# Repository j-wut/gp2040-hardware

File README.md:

# Open Stick Community hardware repo

This repository is a collection of open-source hardware designs which have been submitted to the project.

# Designs

3D Prints

- [3D Printable Stand - Small](/3D%20Prints/3D%20Printable%20Stand/README.md) - Designed by TheTrain
- [3D Printable Stand - Large](/3D%20Prints/3D%20Printable%20Stand/README.md) - Designed by TheTrain
- [3D Printable Fightstick Case](/3D%20Prints/Fightstick%20Case/README.md) - Designed by TheTrain
- [3D Printable Open Stick Mini](/3D%20Prints/Open%20Stick%20Mini/README.md) - Designed by TheTrain
- [3D Printable Fightstick Case XL](/3D%20Prints/Fightstick%20Case/Community%20submissions/3D%20print%20files/Fightstick%20XL/Open%20Stick%20XL%20-%20Main%20Frame%20(x4%20Buttons).stl) - Designed by Lucipher
- [3D Printable Open Stick Modular](/3D%20Prints/Open%20Stick%20Modular%20(OSM)/README.md) - Designed by TheTrain
- [3D Printable Open Stick Modular - Mini](/3D%20Prints/Open%20Stick%20Modular%20-%20Mini%20(OSM-Mini)/README.md) - Designed by TheTrain
- [3D Printable Open Stick Modular - Slim](/3D%20Prints/Open%20Stick%20Modular%20-%20Slim%20(OSM-Slim)/README.md) - Designed by TheTrain
- [3D Printable Open Stick Astro](/3D%20Prints/Open%20Stick%20Astro%20(OSASTRO)/README.md) - Designed by TheTrain
- [3D Printable OSBMX v2 Buttons](/3D%20Prints/OSBMX%20v2/README.md) - Designed by TheTrain
- [3D Printable OSBLP v2 Buttons](/3D%20Prints/OSBLP%20v2/README.md) - Designed by TheTrain
- [3D Printable OSBMX v2 SiTong Edition Buttons](/3D%20Prints/OSBMX%20v2/Community%20submissions/OSBMX%20v2%20-%20SiTong%20Edition/README.md) - Designed by TheTrain (remixed from the OSBLP v2 by TheTrain)
- [3D Printable OSBLP v2 SiTong Edition Buttons](/3D%20Prints/OSBLP%20v2/Community%20submissions/OSBLP%20v2%20-%20SiTong%20Edition/README.md) - Designed by TheTrain (remixed from the OSBLP v2 by TheTrain)
- [3D Printable OSBHE v2 Buttons](/3D%20Prints/OSBHE%20v2/README.md) - Designed by TheTrain
- [3D Printable OSB Plug](/3D%20Prints/OSB%20Plug/README.md) - Designed by TheTrain
- [3D Printable OSB Analog Stick](/3D%20Prints/OSB%20Analog%20Stick/README.md) - Designed by TheTrain
- [Open Source Arcade Stand - OSAS](/3D%20Prints/Open%20Source%20Arcade%20Stand%20(OSAS)/README.md) - Designed by TheTrain

GP2040-CE Official Boards

- [RP2040 Advanced Breakout Board v5.6E with USB Passthrough](/Boards/GP2040-CE%20Official%20Boards/RP2040%20Advanced%20Breakout%20Board/RP2040%20Advanced%20Breakout%20Board%20-%20Passthrough/README.md) - Designed by TheTrain
- [RP2040 Advanced Breakout Board v5.2E (no USB Passthrough)](/Boards/GP2040-CE%20Official%20Boards/RP2040%20Advanced%20Breakout%20Board/RP2040%20Advanced%20Breakout%20Board/README.md) - Designed by TheTrain
- [RP2040 Basic Breakout Board v5.4E with USB Passthrough](/Boards/GP2040-CE%20Official%20Boards/RP2040%20Basic%20Breakout%20Board/RP2040%20Basic%20Breakout%20Board%20-%20Passthrough/README.md) - Designed by TheTrain
- [RP2040 Basic Breakout Board v5.4E (no USB Passthrough)](/Boards/GP2040-CE%20Official%20Boards/RP2040%20Basic%20Breakout%20Board/RP2040%20Basic%20Breakout%20Board/README.md) - Designed by TheTrain
- [RP2040 Mini Breakout Board v7.5E with USB Passthrough](/Boards/GP2040-CE%20Official%20Boards/RP2040%20Mini%20Breakout%20Board/RP2040%20Mini%20Breakout%20Board%20-%20Passthrough/README.md) - Designed by TheTrain
- [RP2040 Mini Breakout Board v7.3E (no USB Passthrough)](/Boards/GP2040-CE%20Official%20Boards/RP2040%20Mini%20Breakout%20Board/RP2040%20Mini%20Breakout%20Board/README.md) - Designed by TheTrain
- [RP2040 Quick Solder Breakout Board v1.0 (no USB Passthrough)](/Boards/GP2040-CE%20Official%20Boards/RP2040%20Quick%20Solder%20Breakout%20Board/README.md) - Designed by TheTrain

GP2040-CE Official Controllers

- [ARC Accessibility Controller](/Boards/GP2040-CE%20Official%20Controllers/ARC%20Accessibility%20Controller/README.md) - Designed by TheTrain
- [Flatbox Rev 5 RGB](/Boards/GP2040-CE%20Official%20Controllers/Flatbox%20Rev%205%20RGB/README.md) - Remixed by TheTrain from the Flatbox Rev 5 by Jfedor
- [Flatbox Rev 5 Passthrough](/Boards/GP2040-CE%20Official%20Controllers/Flatbox%20Rev%205%20Passthrough/README.md) - Remixed by TheTrain from the Flatbox Rev 5 by Jfedor
- [Open_Core0 v2.0](/Boards/GP2040-CE%20Official%20Controllers/Open_Core0/README.md) - Designed by TheTrain
- [Open_Core0 WASD v2.0](/Boards/GP2040-CE%20Official%20Controllers/Open_Core0%20WASD/README.md) - Designed by TheTrain
- [Open_Core0 MIXUP](/Boards/GP2040-CE%20Official%20Controllers/Open_Core0%20MIXUP/README.md) - Designed by TheTrain
- [Zero_Rhythm v1.0](/Boards/GP2040-CE%20Official%20Controllers/Zero%20Rhythm/README.md) - Designed by TheTrain
- [Pocket Pad](/Boards/GP2040-CE%20Official%20Controllers/Pocket%20Pad/README.md) - Designed by TheTrain
- [Pocket Pad WASD](/Boards/GP2040-CE%20Official%20Controllers/Pocket%20Pad%20WASD/README.md) - Designed by TheTrain
- [Mini Pad](/Boards/GP2040-CE%20Official%20Controllers/Mini%20Pad/README.md) - Designed by TheTrain

Retail Stick Replacement Boards

- [Hori Fighting Edge PS3 (FE PS3)](/Boards/Retail%20Stick%20Replacement%20Boards/Hori%20Fighting%20Edge%20PS3%20(FE%20PS3)/README.md) - Designed by TheTrain
- [Hori Fighting Edge PS4 (FE PS4)](/Boards/Retail%20Stick%20Replacement%20Boards/Hori%20Fighting%20Edge%20PS4%20(FE%20PS4)/README.md) - Designed by TheTrain
- [Hori Real Arcade Pro N PS4 (RAP N PS4)](/Boards/Retail%20Stick%20Replacement%20Boards/Hori%20Real%20Arcade%20Pro%20N%20PS4%20(RAP%20N%20PS4)/README.md) - Designed by TheTrain
- [Hori Real Arcade Pro VLX PS3 (RAP VLX PS3)](/Boards/Retail%20Stick%20Replacement%20Boards/Hori%20Real%20Arcade%20Pro%20VLX%20PS3%20(RAP%20VLX%20PS3)/README.md) - Designed by TheTrain
- [SEGA Dreamcast Twin Stick (with USB Passthrough)](/Boards/Retail%20Stick%20Replacement%20Boards/SEGA%20Dreamcast%20Twin%20Stick%20(with%20USB%20Passthrough)/README.md) - Designed by indigotrance

Supported Boards

- [Ghost Auth v2.0](/Boards/Supported%20Boards/Ghost%20Auth/README.md) - Designed by TheTrain
- [GP2040 Keyboard converter](/Boards/Supported%20Boards/GP2040%20Keyboard%20Converter/Waveshare%20Zero-PCB/README.md) - Designed by Infraredaces
- [USB Pasthrough Add-on Board](/Boards/Supported%20Boards/USB%20Passthrough%20Board/README.md) - Designed by TheTrain
- [Tiny USB Hub v1.2 - 2x USB with USB C](/Boards/Supported%20Boards/USB%20Hubs/Tiny%20USB%20Hub%20v1.2e/README.md) - Designed by TheTrain
- [Tiny USB Hub v1.3 - 2x USB Direct Connect](/Boards/Supported%20Boards/USB%20Hubs/Tiny%20USB%20Hub%20v1.3e/README.md) - Designed by TheTrain
- [Tiny USB Hub v1.3 v2 - 2x USB Direct Connect](/Boards/Supported%20Boards/USB%20Hubs/Tiny%20USB%20Hub%20v1.3e%20v2/README.md) - Designed by TheTrain
- [Tiny USB Hub v1.4 - 4x USB Direct Connect](/Boards/Supported%20Boards/USB%20Hubs/Tiny%20USB%20Hub%20v1.4e/README.md) - Designed by TheTrain
- [HE Breakout Board v1.1](/Boards/Supported%20Boards/HE%20Breakout%20Board/README.md) - Designed by TheTrain
- [RPBoy v1.0](/Boards/Supported%20Boards/RPBoy/README.md) - Designed by TheTrain
- [RPBoy Mini v2.0](/Boards/Supported%20Boards/RPBoy%20Mini/README.md) - Designed by TheTrain
- [Key Matrix Diode Adapter](/Boards/Supported%20Boards/Key%20Matrix%20Diode%20Adapter/README.md) - 44-switch keyboard-style matrix with N-key rollover for the RP2040 Advanced Breakout Board (USB Passthrough)

Miscellaneous

- [Haute42/COSMOX Bottom Foam](/Miscellaneous/Haute42%20COSMOX%20Bottom%20Foam/README.md) - Designed by TheTrain
- [Sanjuks V3 AM5 Adapter Plate](/Miscellaneous/Sanjuks%20V3%20AM5%20Adapter%20Plate/README.md) - Designed by TheTrain
- [Sanjuks Style Nobi Topper](/Miscellaneous/Sanjuks%20Style%20Nobi%20Topper/README.md) - Designed by TheTrain
- [Open LED Project - Sanwa 30mm RGB LEDs](/Miscellaneous/Open%20LED%20Project%20-%20Sanwa%2030mm%20RGB%20LED/README.md) - Designed by TheTrain
- [Open LED Project - Addressable RGB LED Light Bar](/Miscellaneous/Open%20LED%20Project%20-%20Addressable%20RGB%20LED%20Light%20Bar/README.md) - Designed by TheTrain
- [Nintendo Switch Art Cart](/Miscellaneous/Nintendo%20Switch%20Art%20Carts/README.md) - Designed by TheTrain, art template by TheTrain
- [Sanwa JLF Plate Cover](/Miscellaneous/Sanwa%20JLF%20Plate%20Cover/README.md) - Designed by TheTrain

Trains Vewlix Stuff

- [Vewlix Coin Return Adapter](/Trains%20Vewlix%20Stuff/Vewlix%20Coin%20Return%20Adapter/README.md) - Designed by TheTrain
- [Vewlix Coin Return Slot](/Trains%20Vewlix%20Stuff/Vewlix%20Coin%20Return%20Slot/README.md) - Designed by TheTrain
- [Vewlix Coin Mech](/Trains%20Vewlix%20Stuff/Vewlix%20Coin%20Mech/README.md) - Designed by TheTrain
- [Vewlix Stickers](/Trains%20Vewlix%20Stuff/Vewlix%20Stickers/README.md) - Remixes and customs by TheTrain
- [Vewlix Control Panel SiTong Adapter Rings](/Trains%20Vewlix%20Stuff/Vewlix%20Control%20Panel%20SiTong%20Adapter%20Rings/README.md) - Designed by TheTrain
- [Vewlix NESiCA NFC Reader](/Trains%20Vewlix%20Stuff/Vewlix%20NESiCA%20NFC%20Reader/README.md) - Designed by TheTrain
- [Vewlix Sub-Panel Art and Cut Files](/Trains%20Vewlix%20Stuff/Vewlix%20Sub-Panel%20Art%20and%20Cut%20Files/README.md) - Designed by Jermaine Davis

Trains Sim Racing Stuff

- [Logitech G PRO RS Wheel Hub wall mount](/Trains%20Sim%20Racing%20Stuff/Logitech%20G%20PRO%20RS%20Wheel%20Hub%20wall%20mount/README.md) - Designed by TheTrain
- [Logitech G PRO RS Wheel Hub 4040 mount](/Trains%20Sim%20Racing%20Stuff/Logitech%20G%20PRO%20RS%20Wheel%20Hub%204040%20mount/README.md) - Designed by TheTrain
- [Logitech G PRO RS Wheel Hub Shifter Pad Mod](/Trains%20Sim%20Racing%20Stuff/Logitech%20RS%20Wheel%20Hub%20Shifter%20Pad%20Mod/README.md) - Designed by TheTrain
- [Logitech G PRO RS Wheel Rim template](/Trains%20Sim%20Racing%20Stuff/Logitech%20G%20PRO%20RS%20Wheel%20Rim%20template/README.md) - Designed by TheTrain
- [Wind Sim](/Trains%20Sim%20Racing%20Stuff/Wind%20Sim/README.md) - Designed by TheTrain
- [LapTimer](/Trains%20Sim%20Racing%20Stuff/Laptimer/README.md) - Designed by TheTrain
- [Porsche GT3 R Plate](/Trains%20Sim%20Racing%20Stuff/Porsche%20911%20GT3%20R%20plate/README.md) - Designed by TheTrain

Trains Theatrhythm Stuff
- [Theatrhythm - All-Star Carnival Manual](/Trains%20Theatrhythm%20Stuff/Theatrhythm%20Manual/Theatrhythm%20-%20All-Star%20Carnival%20-%20Manual.pdf)
- [Theatrhythm - All-Star Carnival JLF Shaft](/Trains%20Theatrhythm%20Stuff/Theatrhythm%20JLF%20shaft/README.md) - Designed by LayerShift
- [Theatrhythm - All-Star Carnival Side Plexi Art](/Trains%20Theatrhythm%20Stuff/Theatrhythm%20ASC%20Arcade%20Cabinet%20Art/Theatrhythm%20ASC%20Side%20Plexi%20Art/README.md) - Designed by TheTrain
- [Theatrhythm - All-Star Carnival Front Control Panel Art](/Trains%20Theatrhythm%20Stuff/Theatrhythm%20ASC%20Arcade%20Cabinet%20Art/Theatrhythm%20ASC%20Front%20Control%20Panel%20Art/README.md) - Designed by TheTrain
- [Theatrhythm - All-Star Carnival NESiCA Reader Art](/Trains%20Theatrhythm%20Stuff/Theatrhythm%20ASC%20Arcade%20Cabinet%20Art/Theatrhythm%20ASC%20NESiCA%20Reader%20Art/README.md) - Designed by TheTrain
- [Theatrhythm - All-Star Carnival Coin Sticker Art](/Trains%20Theatrhythm%20Stuff/Theatrhythm%20ASC%20Arcade%20Cabinet%20Art/Theatrhythm%20ASC%20Coin%20Sticker%20Art/README.md) - Designed by TheTrain

Trains Arcade Machine Manual Stuff

- [Taito Vewlix L - Manual - Part 1](/Trains%20Vewlix%20Stuff/Vewlix%20Manual/Taito%20Vewlix%20L%20-%20Manual%20-%20Part%201.pdf)
- [Taito Vewlix L - Manual - Part 2](/Trains%20Vewlix%20Stuff/Vewlix%20Manual/Taito%20Vewlix%20L%20-%20Manual%20-%20Part%202.pdf)
- [Taito Vewlix L - Manual - Part 3](/Trains%20Vewlix%20Stuff/Vewlix%20Manual/Taito%20Vewlix%20L%20-%20Manual%20-%20Part%203.pdf)
- [Theatrhythm - All-Star Carnival](/Trains%20Theatrhythm%20Stuff/Theatrhythm%20Manual/Theatrhythm%20-%20All-Star%20Carnival%20-%20Manual.pdf)

Tutorials

- [Focus Attack RGB LED Board Configuration](/Tutorials/Focus%20Attack%20LED%20Board%20Configuration/README.md) for the [RP2040 Advanced Breakout Board v5.6](/Boards/GP2040-CE%20Official%20Boards/RP2040%20Advanced%20Breakout%20Board/RP2040%20Advanced%20Breakout%20Board%20-%20Passthrough/README.md) - Written by TheTrain
- [USB Passthrough Add-on Board Installation](/Tutorials/USB%20Passthrough%20Board%20Installation/README.md) - Written by TheTrain
- [Logitech RS Wheel Hub Shifter Pad Mod](/Tutorials/Logitech%20RS%20Wheel%20Hub%20Shifter%20Pad%20Mod/README.md) - Written by TheTrain

Vendor Resources

- [GP2040-CE Logo Files](/Vendor%20Resources/GP2040-CE%20Logo%20files/README.md)

# Contributing

Any design submitted to this repository must be submitted by the original copyright holder and include a [license](#licensing). If your license requires attribution, you must provide details on how to appropriately attribute the design.

# Copyright

All copyrights are retained by the original author(s) unless the copyright is explicitly transferred to the Open Stick Community.

# Licensing

Check the LICENSE of each design for details on how the design can be used.

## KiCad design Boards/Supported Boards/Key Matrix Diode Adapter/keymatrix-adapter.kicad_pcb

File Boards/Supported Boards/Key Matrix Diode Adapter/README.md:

# Key matrix diode adapter

A board that turns the 20-pin header of the **RP2040 Advanced Breakout Board (USB Passthrough edition)** into 44
matrix switch inputs with full N-key rollover: all 15 button pins as 4 rows x 11 columns. It goes with the
`RP2040AdvancedBreakoutBoardUSBPassthroughMatrix` firmware config in
[j-wut/GP2040-CE](https://github.com/j-wut/GP2040-CE) (keyboard matrix support).

- 91 x 93.4 mm, 2 layers, 0.2 mm tracks, all through-hole connectors plus 44 SOD-123 diodes.
- **J1** connects to the breakout board's 20-pin header with a straight 20-pin IDC ribbon cable (pin 1 to pin 1).
- **J2-J5** are two pairs of 20-pin switch connectors (A and B).
- **J6-J13** are screw terminals in four rows, two behind each other on each side of the headers: two per switch, in the same order as the connector pins. The
  last 4 switches are on screw terminals only.
- One 1N4148W diode per switch, already on the board. No diodes are needed in the wiring.

## How a switch is wired

Every switch has a **slot** with two contacts, A and B. Wire the switch between them, either on the connector pair
(pin N on A and pin N on B) or on its two neighbouring screw terminals. Both reach the same switch. A switch has no
polarity, so either wire can go to A.

- **A** goes through the switch's diode to its row.
- **B** is its column. All the B contacts of one column are connected on the board, so a harness can share them.
  A contacts must never be shared.

Do not plug a normal 20-pin button harness (buttons wired to ground) into the switch connectors.

## Slot order

Both pairs have the same order. **Pair 1 follows the breakout's 20-pin header.** Each of its 15 button pins
carries the switch that defaults to that pin's button, so a harness made for the breakout's pinout lines up:

- Pin 5 is K4 (L2), pin 13 is P1 (B3), pin 20 is U (Up), and so on.

The breakout's 5 power and ground positions (pins 1-4 and 9) carry five more switches. Pair 2 carries the next
20 in row order, and the last 4 are on screw terminals only. R*n*C*m* is the switch in row *n*, column *m*, as listed in the web config (Add-ons > Keyboard
Matrix).

| Pin | Pair 1 (J2 A / J3 B) | Pair 2 (J4 A / J5 B) |
|-----|-----|-----|
| 1 | R2C5 | R2C10 |
| 2 | R2C6 | R2C11 |
| 3 | R2C7 | R3C1 |
| 4 | R2C8 | R3C2 |
| 5 | K4 (R1C1) | R3C3 |
| 6 | K3 (R1C2) | R3C4 |
| 7 | K2 (R1C3) | R3C5 |
| 8 | K1 (R1C4) | R3C6 |
| 9 | R2C9 | R3C7 |
| 10 | P4 (R1C5) | R3C8 |
| 11 | P3 (R1C6) | R3C9 |
| 12 | P2 (R1C7) | R3C10 |
| 13 | P1 (R1C8) | R3C11 |
| 14 | S2 (R1C9) | R4C1 |
| 15 | A1 (R1C10) | R4C2 |
| 16 | S1 (R1C11) | R4C3 |
| 17 | L (R2C1) | R4C4 |
| 18 | R (R2C2) | R4C5 |
| 19 | D (R2C3) | R4C6 |
| 20 | U (R2C4) | R4C7 |

Screw terminals only: R4C8, R4C9, R4C10, R4C11.

The screw terminals hold the same slots in the same order, A then B:

- above the headers, wire entry toward the top edge: the front row (at the edge) has pair 1 pins 1-11, the row
  behind it has pair 1 pins 12-20, then R4C8 and R4C9
- below the headers, wire entry toward the bottom edge: the front row (at the edge) has pair 2 pins 1-11, the row
  behind it has pair 2 pins 12-20, then R4C10 and R4C11
- every row reads left to right

Each slot's label is printed just behind its two screws. The rows are 6 mm apart, so the wires for a back row
go in over the diodes of the row in front.

GPIO 20-22 (A2, L3, R3 on the breakout's 4-pin harness) are not on the 20-pin header and stay ordinary buttons on
the breakout board. Don't wire anything else to the breakout's own K1-K4, P1-P4, S1, S2, A1, L, R, D, U terminals
while the adapter is connected: those GPIOs are matrix lines now.

## Signals

| J1 pin | Signal | Breakout label | | J1 pin | Signal | Breakout label |
|-----|--------|----|-|-----|--------|----|
| 1 | +5V | VCC | | 2 | +5V | VCC |
| 3 | GND | G | | 4 | GND | G |
| 5 | COL1 (GP5) | K4 | | 6 | COL2 (GP6) | K3 |
| 7 | COL3 (GP7) | K2 | | 8 | COL4 (GP8) | K1 |
| 9 | GND | G | | 10 | COL5 (GP9) | P4 |
| 11 | COL6 (GP10) | P3 | | 12 | COL7 (GP11) | P2 |
| 13 | COL8 (GP12) | P1 | | 14 | COL9 (GP13) | S2 |
| 15 | COL10 (GP14) | A1 | | 16 | COL11 (GP15) | S1 |
| 17 | ROW1 (GP16) | L | | 18 | ROW2 (GP17) | R |
| 19 | ROW3 (GP18) | D | | 20 | ROW4 (GP19) | U |

The pin numbers are the pad numbers of the 20-pin header on the breakout board's own design file (v5.6, in this
repository): pins 1 and 2 are +5 V, pin 20 is UP. `check.py` reads that file and checks J1 against it. Check pin 1
on your board before the first power-up anyway.

## Files

| File | What it is |
|------|------------|
| `keymatrix-adapter.kicad_sch`, `.kicad_pcb`, `.kicad_pro` | KiCad 7 project |
| `fab/gerbers/` | Gerbers and drill file for ordering the PCB |
| `fab/keymatrix-adapter-bom.csv` | Bill of materials |
| `fab/keymatrix-adapter-pos.csv` | Pick-and-place positions for the diodes |
| `fab/keymatrix-adapter-schematic.pdf` | Schematic |
| `generate.py`, `autoroute.py` | Build the schematic and the routed PCB from one parts and nets table |
| `check.py` | Runs the checks below and writes `fab/` |
| `simulate.py`, `sim-results.txt` | ngspice simulation of the full matrix through this board, and its results |

## Checks

`python3 generate.py && python3 check.py [path/to/GP2040-CE]` (needs KiCad 7 with its Python module) regenerates the
design and checks:

- J1's pin numbers match the 20-pin header on the breakout board's design file in this repository.
- KiCad DRC: no clearance or other violations, no unconnected pads.
- The schematic netlist (from `kicad-cli`) connects exactly the same pads as the PCB.
- Every one of the 44 switches has its own diode, cathode on the right row. Given a GP2040-CE checkout, the rows and
  columns must also match `KEY_MATRIX_ROW_PINS` / `KEY_MATRIX_COL_PINS` in the firmware board config.
- Every switch is on exactly one connector slot. Pair 1 is in breakout pin order. The screw terminals, read around
  the board, are in the same slot order as the connectors, with the terminal-only switches in order between them.

## Simulation

`python3 simulate.py` runs ngspice on the whole 4 x 11 matrix through this board: RP2040 pull-ups and pins, the ribbon
cable, the copper of every net on this PCB (measured from the board file), the 44 diodes, and the harness wiring
(each switch's own wire plus the column's B wire daisy-chained through its four switches). It scans the way the firmware
does and checks every read for several held-switch patterns, including all 44 held. Results:
[sim-results.txt](sim-results.txt).

| Wiring (ribbon / switch wire / column chain) | Press seen at the pin | Column recovery | Result with defaults |
|-----|-----|-----|-----|
| short: 0.15 m / 0.2 m / 1 m | 0.2 us | up to 10 us | pass |
| typical arcade stick: 0.3 m / 0.5 m / 3 m | 0.3 us | up to 19 us | pass |
| long cabinet: 1 m / 1 m / 6 m | 0.6 us | up to 34 us | pass |

`python3 simulate.py --trace trace.json` replays a GPIO timeline recorded from the firmware's own scan loop
instead of the fixed schedule: row drive and release events plus read times in, the voltage and logic level of
every column at each read out. The input format is in `run_trace()`.

Wire length adds no meaningful latency: a press shows up at the pin in under 0.6 us even with cabinet
wiring. What wiring does set is how long a released row's columns take to climb back through the RP2040's weak
pull-ups. The firmware waits a fixed **row delay** after each row for that (default 50 us, set in the web config
next to the settle time). With the defaults a full scan of all four rows takes about 224 us, well inside the 1 ms
between USB reports. Shorter wiring can use a smaller row delay; see `docs/keymatrix-sim/results.txt` in the firmware repository.

Not built or tested on hardware yet.

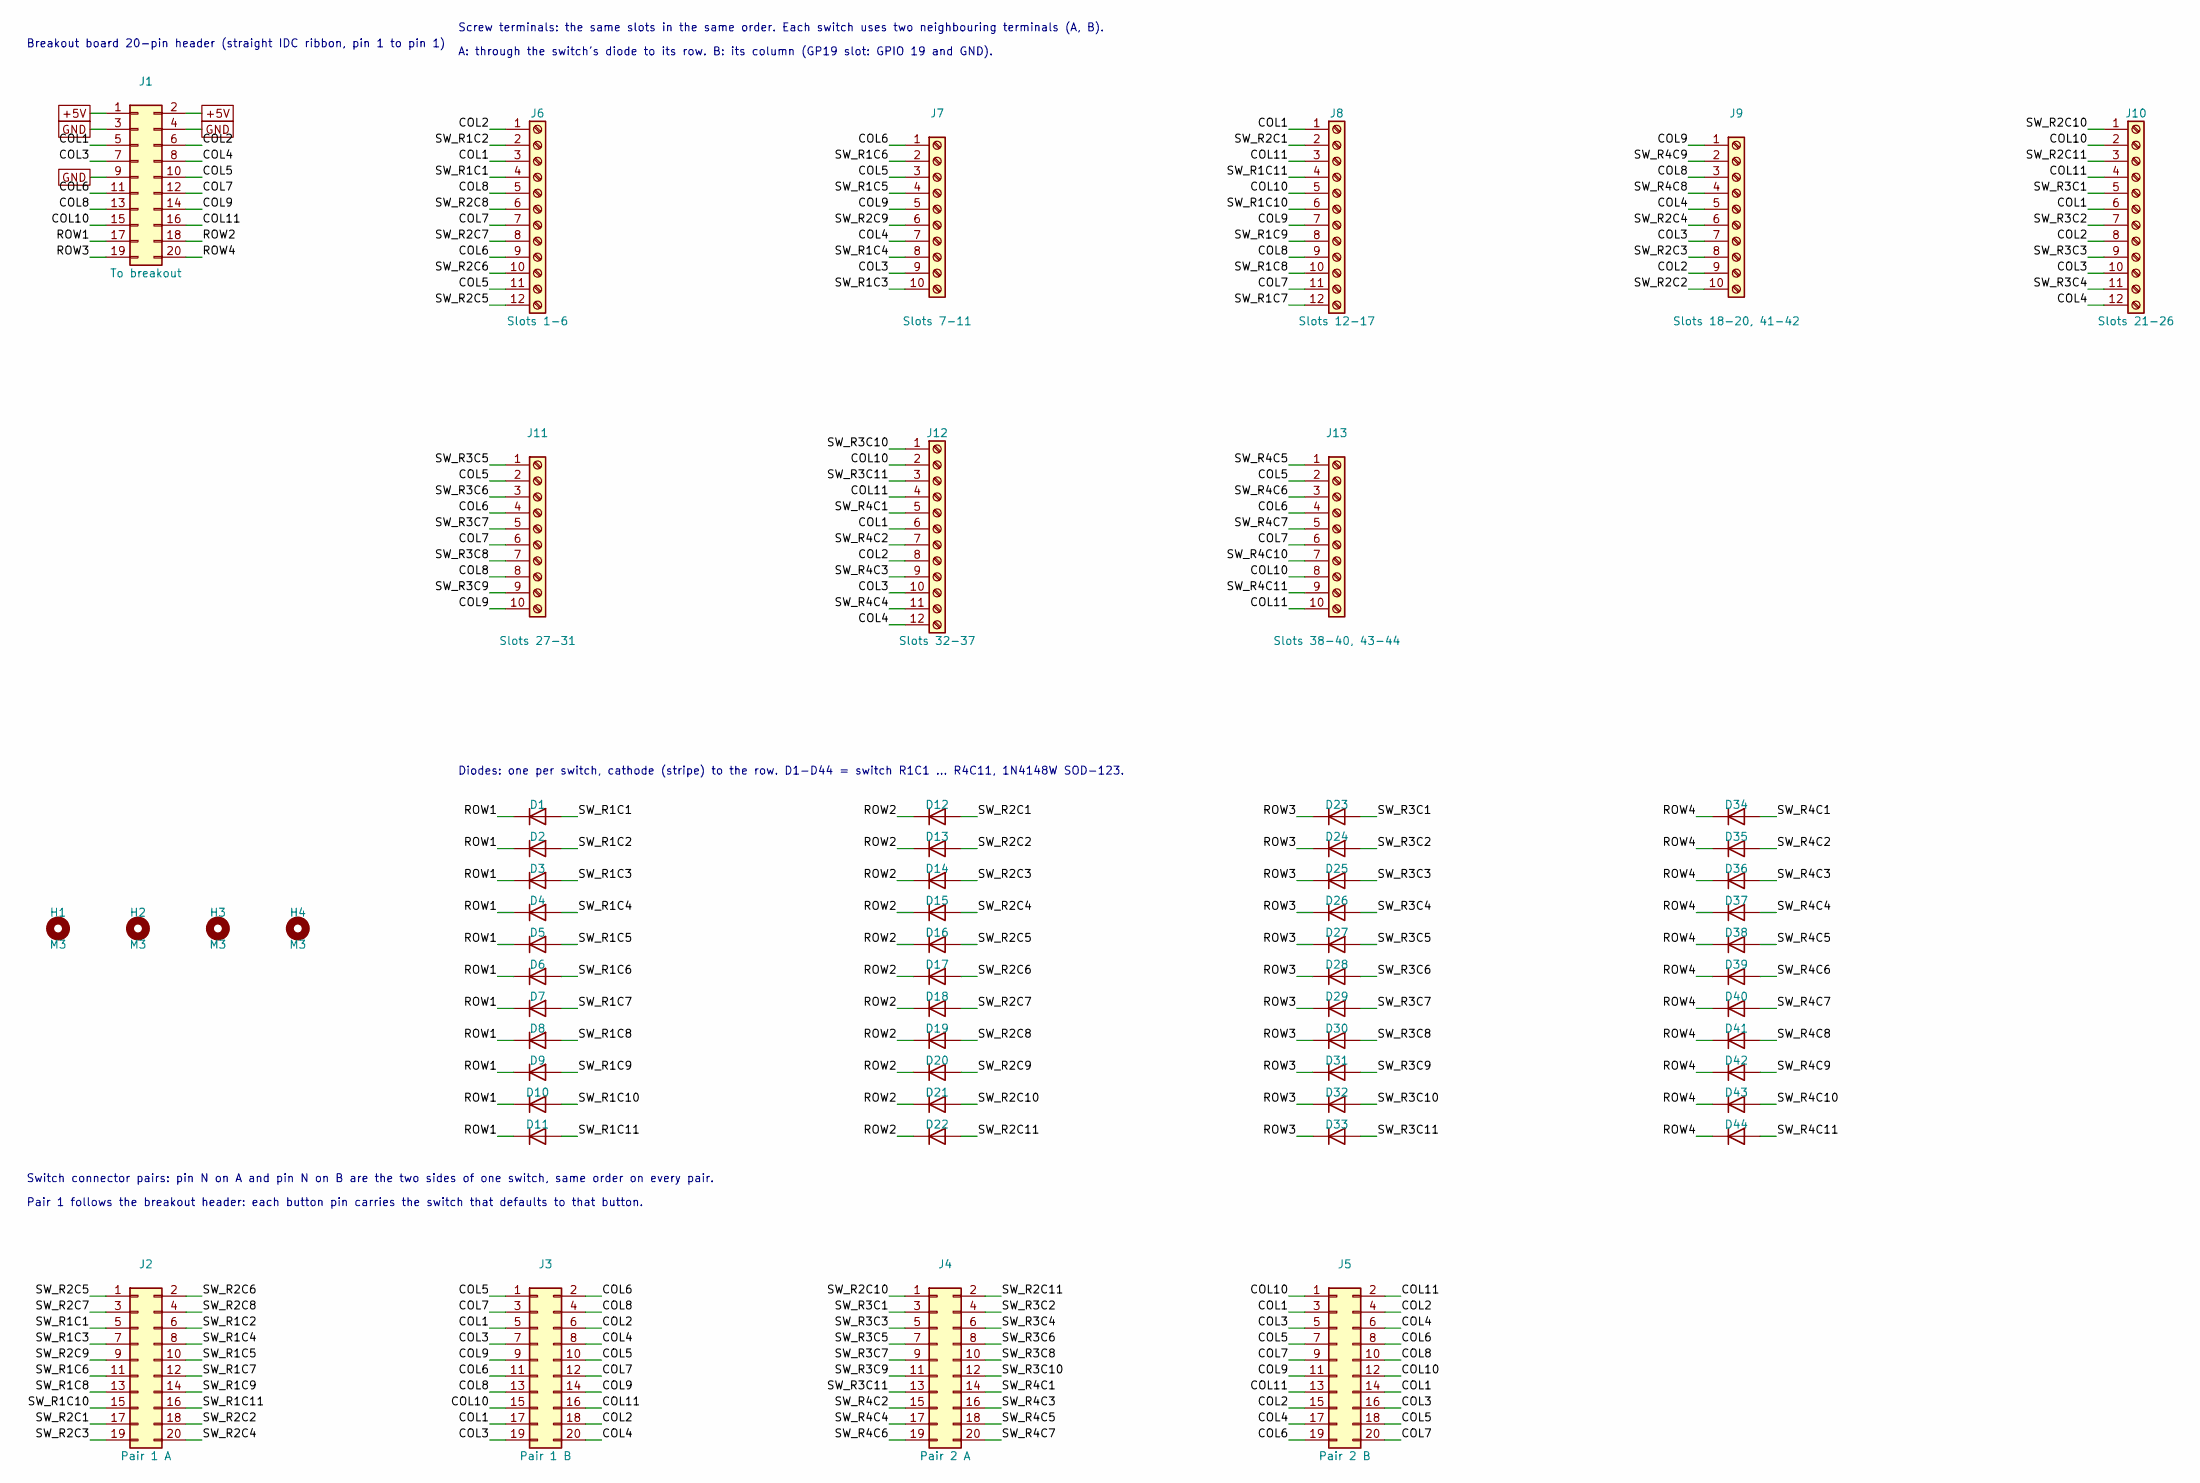
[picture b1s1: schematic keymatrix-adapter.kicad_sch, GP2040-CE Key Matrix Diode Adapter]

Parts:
D1, D2, D3, D4, D5, D6, D7, D8, D9, D10, D11, D12, D13, D14, D15, D16, D17, D18, D19, D20, D21, D22, D23, D24, D25, D26, D27, D28, D29, D30, D31, D32, D33, D34, D35, D36, D37, D38, D39, D40, D41, D42, D43, D44: 1N4148W; D_SOD-123
H1, H2, H3, H4: M3; MountingHole_3.2mm_M3
J1: To breakout; IDC-Header_2x10_P2.54mm_Vertical
J2: Pair 1 A; IDC-Header_2x10_P2.54mm_Vertical
J3: Pair 1 B; IDC-Header_2x10_P2.54mm_Vertical
J4: Pair 2 A; IDC-Header_2x10_P2.54mm_Vertical
J5: Pair 2 B; IDC-Header_2x10_P2.54mm_Vertical
J6: Slots 1-6; TerminalBlock_Phoenix_PT-1,5-12-3.5-H_1x12_P3.50mm_Horizont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
J7: Slots 7-11; TerminalBlock_Phoenix_PT-1,5-10-3.5-H_1x10_P3.50mm_Horizont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
J8: Slots 12-17; TerminalBlock_Phoenix_PT-1,5-12-3.5-H_1x12_P3.50mm_Horizont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
J9: Slots 18-20, 41-42; TerminalBlock_Phoenix_PT-1,5-10-3.5-H_1x10_P3.50mm_Horizont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
J10: Slots 21-26; TerminalBlock_Phoenix_PT-1,5-12-3.5-H_1x12_P3.50mm_Horizont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
J11: Slots 27-31; TerminalBlock_Phoenix_PT-1,5-10-3.5-H_1x10_P3.50mm_Horizont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
J12: Slots 32-37; TerminalBlock_Phoenix_PT-1,5-12-3.5-H_1x12_P3.50mm_Horizont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
J13: Slots 38-40, 43-44; TerminalBlock_Phoenix_PT-1,5-10-3.5-H_1x10_P3.50mm_Horizont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

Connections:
+5V: J1.1, J1.2
COL1: J1.5, J3.5, J3.17, J5.3, J5.14, J6.3, J8.1, J10.6, J12.6
COL2: J1.6, J3.6, J3.18, J5.4, J5.15, J6.1, J9.9, J10.8, J12.8
COL3: J1.7, J3.7, J3.19, J5.5, J5.16, J7.9, J9.7, J10.10, J12.10
COL4: J1.8, J3.8, J3.20, J5.6, J5.17, J7.7, J9.5, J10.12, J12.12
COL5: J1.10, J3.1, J3.10, J5.7, J5.18, J6.11, J7.3, J11.2, J13.2
COL6: J1.11, J3.2, J3.11, J5.8, J5.19, J6.9, J7.1, J11.4, J13.4
COL7: J1.12, J3.3, J3.12, J5.9, J5.20, J6.7, J8.11, J11.6, J13.6
COL8: J1.13, J3.4, J3.13, J5.10, J6.5, J8.9, J9.3, J11.8
COL9: J1.14, J3.9, J3.14, J5.11, J7.5, J8.7, J9.1, J11.10
COL10: J1.15, J3.15, J5.1, J5.12, J8.5, J10.2, J12.2, J13.8
COL11: J1.16, J3.16, J5.2, J5.13, J8.3, J10.4, J12.4, J13.10
GND: J1.3, J1.4, J1.9
ROW1: D1.1 (K), D2.1 (K), D3.1 (K), D4.1 (K), D5.1 (K), D6.1 (K), D7.1 (K), D8.1 (K), D9.1 (K), D10.1 (K), D11.1 (K), J1.17
ROW2: D12.1 (K), D13.1 (K), D14.1 (K), D15.1 (K), D16.1 (K), D17.1 (K), D18.1 (K), D19.1 (K), D20.1 (K), D21.1 (K), D22.1 (K), J1.18
ROW3: D23.1 (K), D24.1 (K), D25.1 (K), D26.1 (K), D27.1 (K), D28.1 (K), D29.1 (K), D30.1 (K), D31.1 (K), D32.1 (K), D33.1 (K), J1.19
ROW4: D34.1 (K), D35.1 (K), D36.1 (K), D37.1 (K), D38.1 (K), D39.1 (K), D40.1 (K), D41.1 (K), D42.1 (K), D43.1 (K), D44.1 (K), J1.20
SW_R1C1: D1.2 (A), J2.5, J6.4
SW_R1C2: D2.2 (A), J2.6, J6.2
SW_R1C3: D3.2 (A), J2.7, J7.10
SW_R1C4: D4.2 (A), J2.8, J7.8
SW_R1C5: D5.2 (A), J2.10, J7.4
SW_R1C6: D6.2 (A), J2.11, J7.2
SW_R1C7: D7.2 (A), J2.12, J8.12
SW_R1C8: D8.2 (A), J2.13, J8.10
SW_R1C9: D9.2 (A), J2.14, J8.8
SW_R1C10: D10.2 (A), J2.15, J8.6
SW_R1C11: D11.2 (A), J2.16, J8.4
SW_R2C1: D12.2 (A), J2.17, J8.2
SW_R2C2: D13.2 (A), J2.18, J9.10
SW_R2C3: D14.2 (A), J2.19, J9.8
SW_R2C4: D15.2 (A), J2.20, J9.6
SW_R2C5: D16.2 (A), J2.1, J6.12
SW_R2C6: D17.2 (A), J2.2, J6.10
SW_R2C7: D18.2 (A), J2.3, J6.8
SW_R2C8: D19.2 (A), J2.4, J6.6
SW_R2C9: D20.2 (A), J2.9, J7.6
SW_R2C10: D21.2 (A), J4.1, J10.1
SW_R2C11: D22.2 (A), J4.2, J10.3
SW_R3C1: D23.2 (A), J4.3, J10.5
SW_R3C2: D24.2 (A), J4.4, J10.7
SW_R3C3: D25.2 (A), J4.5, J10.9
SW_R3C4: D26.2 (A), J4.6, J10.11
SW_R3C5: D27.2 (A), J4.7, J11.1
SW_R3C6: D28.2 (A), J4.8, J11.3
SW_R3C7: D29.2 (A), J4.9, J11.5
SW_R3C8: D30.2 (A), J4.10, J11.7
SW_R3C9: D31.2 (A), J4.11, J11.9
SW_R3C10: D32.2 (A), J4.12, J12.1
SW_R3C11: D33.2 (A), J4.13, J12.3
SW_R4C1: D34.2 (A), J4.14, J12.5
SW_R4C2: D35.2 (A), J4.15, J12.7
SW_R4C3: D36.2 (A), J4.16, J12.9
SW_R4C4: D37.2 (A), J4.17, J12.11
SW_R4C5: D38.2 (A), J4.18, J13.1
SW_R4C6: D39.2 (A), J4.19, J13.3
SW_R4C7: D40.2 (A), J4.20, J13.5
SW_R4C8: D41.2 (A), J9.4
SW_R4C9: D42.2 (A), J9.2
SW_R4C10: D43.2 (A), J13.7
SW_R4C11: D44.2 (A), J13.9

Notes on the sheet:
Breakout board 20-pin header (straight IDC ribbon, pin 1 to pin 1)
Switch connector pairs: pin N on A and pin N on B are the two sides of one switch, same order on every pair.
Pair 1 follows the breakout header: each button pin carries the switch that defaults to that button.
Screw terminals: the same slots in the same order. Each switch uses two neighbouring terminals (A, B).
A: through the switch's diode to its row. B: its column (GP19 slot: GPIO 19 and GND).
Diodes: one per switch, cathode (stripe) to the row. D1-D44 = switch R1C1 ... R4C11, 1N4148W SOD-123.

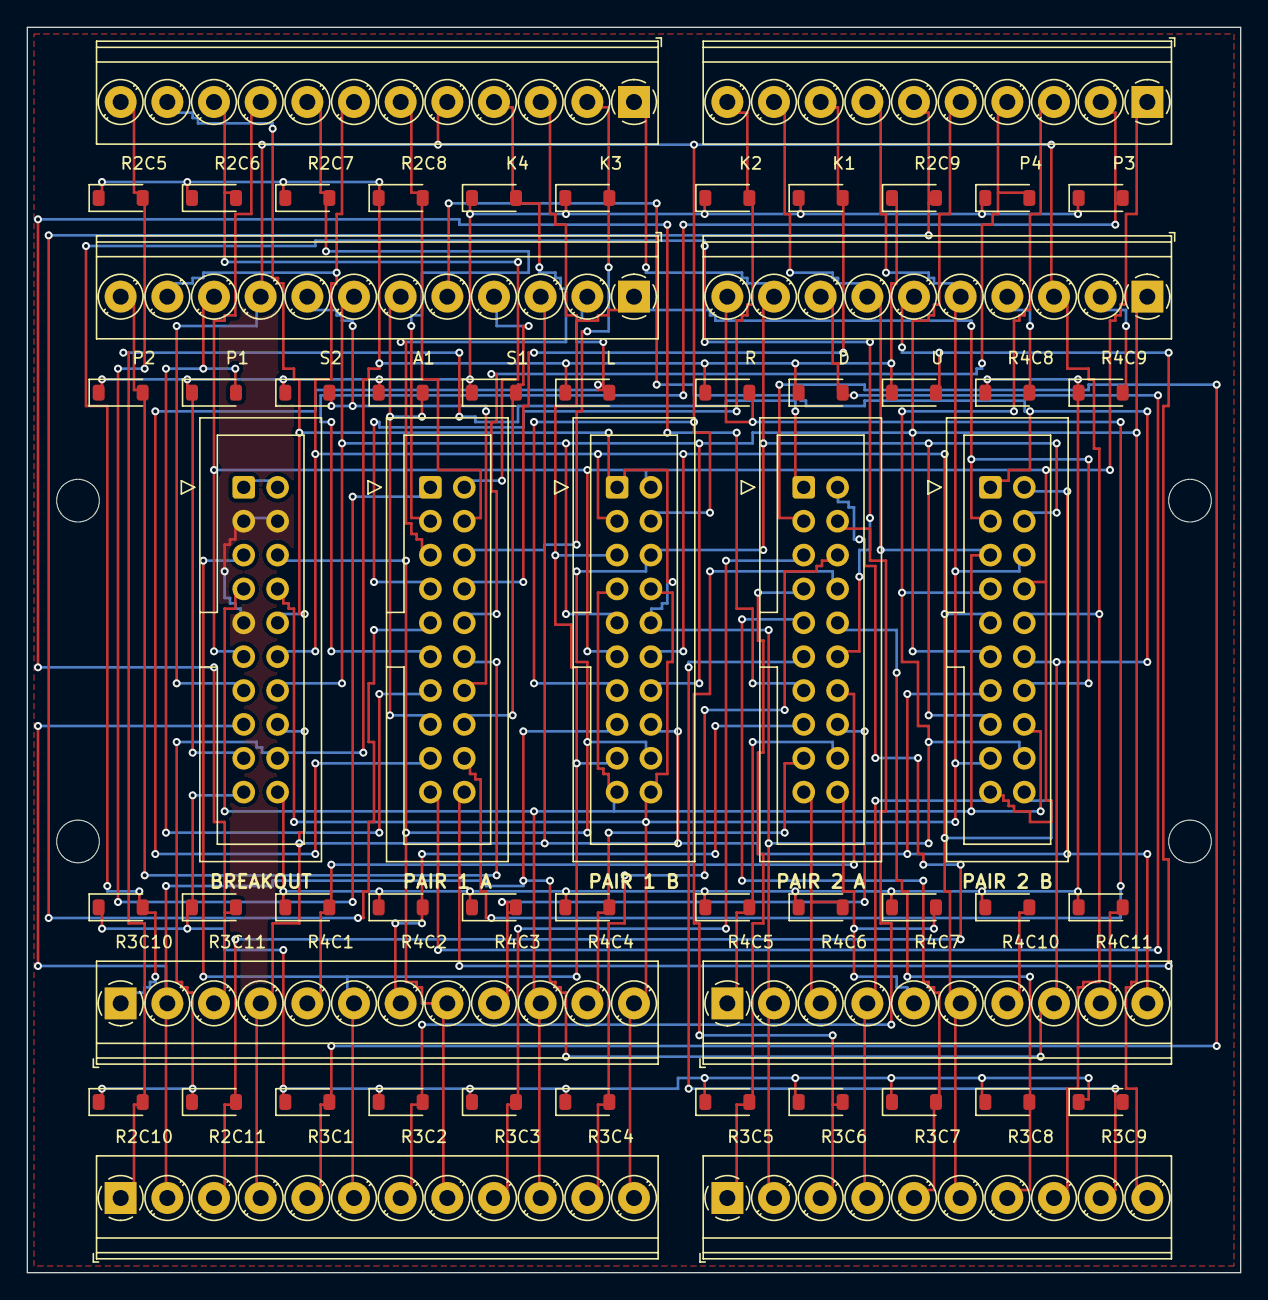
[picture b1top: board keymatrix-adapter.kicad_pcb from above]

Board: 2 copper layers, 91.0 x 93.4 mm, 61 parts (0 on the bottom side), 61 nets.

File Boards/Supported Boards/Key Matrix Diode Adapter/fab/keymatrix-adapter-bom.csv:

Qty,References,Value,Footprint,Description
5,J1 J2 J3 J4 J5,2x10 box header,Connector_IDC:IDC-Header_2x10_P2.54mm_Vertical,"2.54 mm shrouded IDC box header, vertical, through-hole"
4,J6 J8 J10 J12,12-way terminal,"TerminalBlock_Phoenix:TerminalBlock_Phoenix_PT-1,5-12-3.5-H_1x12_P3.50mm_Horizontal","3.5 mm pitch screw terminal, Phoenix PT 1,5/12-3,5-H or equivalent"
4,J7 J9 J11 J13,10-way terminal,"TerminalBlock_Phoenix:TerminalBlock_Phoenix_PT-1,5-10-3.5-H_1x10_P3.50mm_Horizontal","3.5 mm pitch screw terminal, Phoenix PT 1,5/10-3,5-H or equivalent"
44,D1 D2 D3 D4 D5 D6 D7 D8 D9 D10 D11 D12 D13 D14 D15 D16 D17 D18 D19 D20 D21 D22 D23 D24 D25 D26 D27 D28 D29 D30 D31 D32 D33 D34 D35 D36 D37 D38 D39 D40 D41 D42 D43 D44,1N4148W,Diode_SMD:D_SOD-123,"Small-signal switching diode, SOD-123"
